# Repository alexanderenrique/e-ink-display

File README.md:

# E-Ink Display

A custom ESP32-C3-based e-ink display platform with a modular app system, BLE configuration, OTA updates, and three KiCad PCB variants. Built around the Seeed XIAO ESP32-C3 and a 2.9" tri-color (black/white/red) e-ink panel (e.g. GDEM029C90).

## Licensing

Hardware design files in [`e-ink-PCBs/`](e-ink-PCBs/) are licensed under **CERN-OHL-W-2.0**. Firmware, scripts, config examples, and Markdown documentation are under the **MIT License**. See [`LICENSE`](LICENSE), [`LICENSE-HARDWARE`](LICENSE-HARDWARE), and [`LICENSE-SOFTWARE`](LICENSE-SOFTWARE).

## Open source scope (third-party parts)

This project is shared to meet the [Open Source Hardware Definition](https://www.oshwa.org/definition/) and aligns with the spirit of [OSHWA certification requirements](https://certification.oshwa.org/requirements.html) for distinguishing parts outside the licensor’s control.

**Released under the licenses above (our work):**

- Schematics and PCB layouts in [`e-ink-PCBs/`](e-ink-PCBs/) (native KiCad sources and Gerber exports in each variant folder).
- Firmware in [`e-ink_code/firmware/`](e-ink_code/firmware/), plus tooling in [`e-ink_code/scripts/`](e-ink_code/scripts/) and examples under [`e-ink_code/config/`](e-ink_code/config/).

**Not open-sourced by this repository (standard commercial / third-party parts; use vendor documentation):**

| Item | Role | Public datasheet / info |
|------|------|-------------------------|
| Seeed XIAO ESP32-C3 | MCU module (ESP32-C3, crystal, antenna, regulators inside module) | Seeed Wiki and [ESP32-C3 technical reference](https://www.espressif.com/en/products/socs/esp32-c3) |
| GDEM029C90 (or compatible Good Display panel) | E-ink panel + timing/controller as supplied by vendor | Vendor PDF (e.g. Good Display product pages) |
| SHT31 | Temperature / humidity sensor IC or module | [Sensirion SHT31 datasheet](https://www.sensirion.com/) |
| FQP27P06, ZXMP4A16G | Discrete MOSFETs | [ON Semi FQP27P06](https://www.onsemi.com/), [Diodes ZXMP4A16G](https://www.diodes.com/) |
| MCP7940N (RTC variant only) | I2C real-time clock | [Microchip MCP7940N](http://ww1.microchip.com/downloads/en/DeviceDoc/20005010F.pdf) |

Optional firmware features (e.g. the **shelf** app) may call HTTP APIs or a companion script (`bin_lookup_server.py`); the hardware and core firmware remain usable without those services.

## Project structure

```
e-ink-display/
├── e-ink-PCBs/                 # KiCad 9 hardware + Gerbers
│   ├── SMD/                    # “SMD” layout variant
│   ├── Throughole-Basic/       # Through-hole, base design
│   ├── Throughole-RTC/         # Through-hole + MCP7940N RTC (+ optional SD header in sch)
│   └── bom/                    # CSV BOM summaries (regenerate from KiCad after edits)
├── e-ink_code/                 # Firmware and scripts (PlatformIO)
│   ├── firmware/               # ESP32-C3 source, core/, apps/, main.cpp
│   ├── scripts/               # OTA, flash, BLE utilities
│   ├── config/examples/       # Device JSON examples
│   ├── platformio.ini
│   └── requirements.txt       # Python deps for helper scripts
├── docs/
│   └── images/                # Add board photos or renders here (recommended for makers)
├── LICENSE, LICENSE-HARDWARE, LICENSE-SOFTWARE, README.md
```

## Hardware

### Components

| Component | Description |
|-----------|-------------|
| Seeed XIAO ESP32-C3 | Microcontroller with WiFi and BLE |
| GDEM029C90 | 2.9" 128×296 tri-color e-ink display (black/white/red) |
| SHT31 | I2C temperature and humidity sensor |
| FQP27P06 (and variants may add ZXMP4A16G) | P-channel MOSFETs for power switching |
| 100 µF capacitor | Bulk decoupling (where present in schematic) |
| Resistors | Voltage divider (47 kΩ / 68 kΩ), pull-ups, etc. (see BOM CSVs) |
| Battery connector | LiPo / battery input |
| Through-hole RTC add-ons (Throughole-RTC only) | MCP7940N, 32.768 kHz crystal, load caps; optional SD header in schematic |

### Pin mapping (ESP32-C3)

| Pin | Function |
|-----|-----------|
| GPIO 3 | SPI SCK (e-ink) |
| GPIO 4 | SPI MOSI (e-ink) |
| GPIO 7 | e-ink CS |
| GPIO 6 | e-ink DC |
| GPIO 5 | e-ink RST |
| GPIO 21 | e-ink BUSY |
| GPIO 9 | I2C SDA (SHT31) |
| GPIO 10 | I2C SCL (SHT31) |
| GPIO 2 | Battery ADC (voltage divider) |
| GPIO 8 | Display + sensor power MOSFET gate |
| GPIO 20 | Battery divider sense enable (`V_SWITCH`) |

### PCB variants

| Directory | Description |
|-----------|-------------|
| [`e-ink-PCBs/SMD/`](e-ink-PCBs/SMD/) | Single main FQP27P06 switch; mixed THT footprints on some passives as in schematic |
| [`e-ink-PCBs/Throughole-Basic/`](e-ink-PCBs/Throughole-Basic/) | Through-hole friendly; includes ZXMP4A16G + FQP27P06 in schematic |
| [`e-ink-PCBs/Throughole-RTC/`](e-ink-PCBs/Throughole-RTC/) | Basic topology + MCP7940N RTC, crystal, optional `J6` SD block |

Each folder contains `.kicad_pro`, `.kicad_sch`, `.kicad_pcb`, drill files, and `*.gbr` / `*.gbrjob` fab outputs. **Preferred source for modification is KiCad**, not Gerbers alone.

### Replication: BOM and assembly

1. Open the variant you are building and use **Tools → Generate Bill of Materials** in KiCad to export a fresh CSV when anything changes.
2. Human-readable summaries for each variant live in [`e-ink-PCBs/bom/`](e-ink-PCBs/bom/) — see [`e-ink-PCBs/bom/README.md`](e-ink-PCBs/bom/README.md).
3. Order PCBs using the `e-ink_PCB-job.gbrjob` or individual Gerbers in that variant’s folder.
4. Solder power, MCU module, and display connector before first power-on; double-check battery polarity and MOSFET orientation against the silkscreen.
5. **First firmware:** flash over USB with PlatformIO (see **Build and flash** below) or keep a personal `e-ink_code/FLASH_INSTRUCTIONS.md` locally (that filename is gitignored).
6. **Photos / renders:** add PNGs under [`docs/images/`](docs/images/) (e.g. bare PCB, populated board, enclosure) so others can verify the build.

## Firmware

### Architecture

The firmware uses a plugin-based app system. Core managers handle hardware (WiFi, display, power, OTA, BLE) and are injected into apps via dependency injection. Each app implements the `AppInterface` and is registered with the `AppManager`, which coordinates lifecycle and configuration.

```
Main  -->  AppManager  -->  [Fun | Sensor | Shelf | Messages]
                |
           Core Managers
       (WiFi, Display, Power, OTA, BLE)
```

### Apps

| App | Description |
|-----|-------------|
| **fun** | Cycles through cat facts, earthquake data, ISS location, useless facts, and local room temperature/humidity. Rotates display mode across deep sleep cycles. |
| **sensor** | Reads temperature and humidity from the SHT31 sensor, displays on screen, and optionally posts data to a Nemo API endpoint. Supports Celsius/Fahrenheit. |
| **shelf** | Queries a bin lookup server to display shelf/bin owner information. Designed for lab inventory labeling. |
| **messages** | Displays a configurable list of up to 10 messages, cycling through them on each wake. |

### BLE configuration

On cold boot (power-on reset), the device advertises via BLE for up to 3 minutes. A BLE central (phone app, script, etc.) can connect and send a JSON configuration including WiFi credentials, app selection, and app-specific settings. The configuration is stored in NVS (non-volatile storage) and persists across deep sleep and reboots.

### Power management

- Battery voltage is read through a 47k/68k resistor divider on GPIO 2.
- Deep sleep is used between display refreshes (configurable per app).
- When battery drops below 5%, the device shows a low-battery message and enters a periodic wake-check sleep (every 5 minutes). Normal operation resumes at 15%.

### OTA updates

The firmware supports HTTPS OTA updates. A deploy script builds the firmware, generates a manifest (version + SHA256), and uploads it to a remote server. Devices check for updates and apply them over WiFi.

### Build environments

Each app has its own PlatformIO build environment that only compiles the code for that specific app:

| Environment | App | Build flag |
|-------------|-----|------------|
| `seeed_xiao_esp32c3` | All apps | (none) |
| `seeed_xiao_fun` | Fun | `-DAPP_FUN` |
| `seeed_xiao_sensor` | Sensor | `-DAPP_SENSOR` |
| `seeed_xiao_shelf` | Shelf | `-DAPP_SHELF` |
| `seeed_xiao_messages` | Messages | `-DAPP_MESSAGES` |

### Dependencies

Managed by PlatformIO (`lib_deps` in `platformio.ini`):

- [GxEPD2](https://github.com/ZinggJM/GxEPD2) — E-ink display driver
- [ArduinoJson](https://github.com/bblanchon/ArduinoJson) ^6.21.3 — JSON parsing
- [Adafruit SHT31 Library](https://github.com/adafruit/Adafruit_SHT31) ^2.2.2 — Temperature/humidity sensor
- [Adafruit Unified Sensor](https://github.com/adafruit/Adafruit_Sensor) ^1.1.9 — Sensor abstraction
- [NimBLE-Arduino](https://github.com/h2zero/NimBLE-Arduino) ^1.4.1 — BLE stack

## Scripts

Located in `e-ink_code/scripts/`:

| Script | Description |
|--------|-------------|
| `deploy_ota.sh` | Build firmware, create manifest, and SCP to OTA server |
| `flash_firmware.sh` | Flash firmware to ESP32-C3 via USB using esptool |
| `bin_lookup_server.py` | Python HTTP server that proxies NEMO API bin/user data for the shelf app |
| `scan_ble.py` | BLE scanner utility to discover and inspect nearby devices |
| `post_build.py` | Copies built firmware binary to `ota/` directory |
| `make_manifest.py` | Generates `manifest.json` with version and SHA256 hash |

## OSHWA certification (administrative next steps)

After this repository reflects the licenses and documentation above, **certification itself is completed on OSHWA’s site**, not in git:

1. Review [Certification requirements](https://certification.oshwa.org/requirements.html) and the [Open Source Hardware checklist](https://www.oshwa.org/resources/open-source-hardware-checklist).
2. Complete the **Certification Mark License Agreement** and submit documentation links for each hardware version you certify.
3. **Register each unique product** that will carry the certification mark, and follow OSHWA’s **mark usage guidelines** (do not imply endorsement by Seeed, Sensirion, Microchip, OSHWA, etc., beyond factual compatibility).
4. Plan for **annual renewal** emails from OSHWA to reaffirm compliance.

Silkscreen and marketing should use only trademarks you are entitled to; third-party logos on the PCB must be cleared separately from this project’s open-license grants.

## Getting started

### Prerequisites

- [PlatformIO](https://platformio.org/) (CLI or IDE plugin)
- [KiCad](https://www.kicad.org/) 9+ (matches current `.kicad_*` schema)
- Python 3 (for utility scripts)

### Build and flash

```bash
cd e-ink_code

# Build a specific app
pio run -e seeed_xiao_sensor

# Upload via USB
pio run -e seeed_xiao_sensor --target upload

# Monitor serial output
pio device monitor
```

### Deploy OTA update

```bash
cd e-ink_code
./scripts/deploy_ota.sh sensor
```

### Run the bin lookup server (shelf app)

```bash
cd e-ink_code
pip install requests python-dotenv
# Set NEMO_API_KEY in a .env file
python scripts/bin_lookup_server.py
```

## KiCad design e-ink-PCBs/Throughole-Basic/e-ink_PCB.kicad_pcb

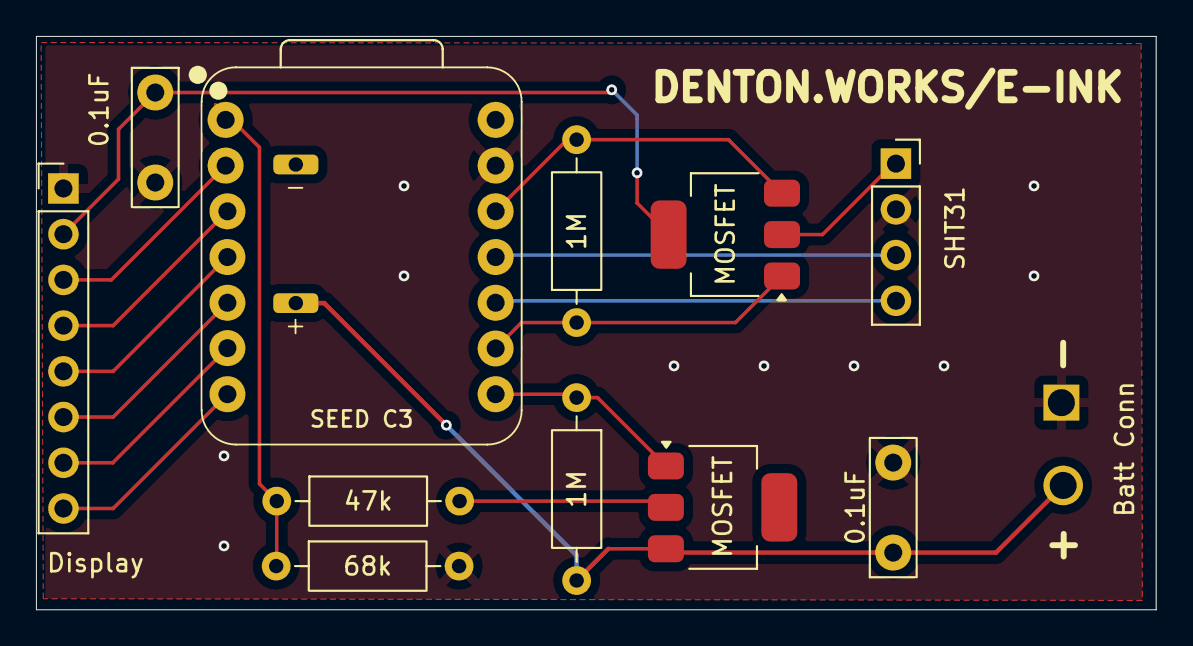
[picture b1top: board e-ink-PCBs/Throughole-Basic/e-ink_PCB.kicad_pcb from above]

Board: 2 copper layers, 62.2 x 31.9 mm, 12 parts (0 on the bottom side), 16 nets.

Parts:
0.1uF, 0.1uF#2: C_Small_US; C_Disc_D7.5mm_W5.0mm_P5.00mm
1M, 47k, 68k: R_Axial_DIN0207_L6.3mm_D2.5mm_P10.16mm_Horizontal
1M#2: 1M; R_Axial_DIN0207_L6.3mm_D2.5mm_P10.16mm_Horizontal
J1: SEED C3; XIAO-ESP32C3-Throughole_alex
J2: e-ink-display; PinHeader_1x08_P2.54mm_Vertical
J3: SHT31; PinSocket_1x04_P2.54mm_Vertical
J5: Batt Conn; PinSocket_1x02_P2.00mm_Vertical
MOSFET: FQP27P06; SOT-223
Q2: MOSFET; SOT-223

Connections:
GND: 0.1uF.2, 0.1uF#2.1, 68k.2, J1.GND (Pin_2), J2.GND (Pin_1), J3.GND (Pin_2), J5.1
unnamed: 47k.1, 68k.1, J1.2 (Pin_8)
unnamed: 0.1uF#2.2, J2.VCC (Pin_2), J3.VIN (Pin_1), Q2.2 (D)
unnamed: J1.3 (Pin_7), J2.SCL (Pin_3)
unnamed: J1.4 (Pin_6), J2.SDA (Pin_4)
unnamed: J1.5, J2.RES (Pin_5)
unnamed: J1.6 (Pin_4), J2.DC (Pin_6)
unnamed: J1.7 (Pin_3), J2.CS (Pin_7)
unnamed: J1.21 (Pin_2), J2.BUSY (Pin_8)
unnamed: J1.10 (Pin_4), J3.SCL (Pin_3)
unnamed: J1.9 (Pin_5), J3.SDA (Pin_4)
unnamed: 0.1uF.1, 1M#2.2, J1.BAT+ (Pin_1), J5.2, MOSFET.3 (S)
unnamed: 47k.2, MOSFET.2 (D)
unnamed: 1M#2.1, J1.20 (Pin_7), MOSFET.1 (G)
unnamed: 1M.1, J1.8 (Pin_6), Q2.1 (G)
unnamed: 1M.2, J1.3.3V (Pin_3), Q2.3 (S)

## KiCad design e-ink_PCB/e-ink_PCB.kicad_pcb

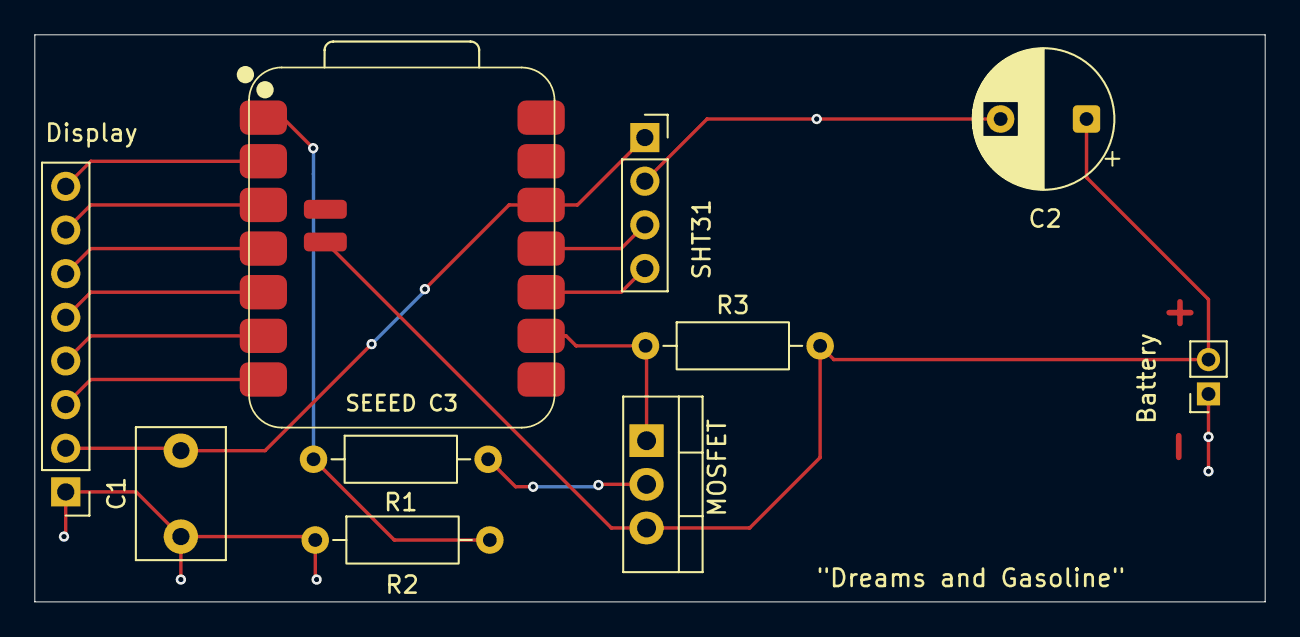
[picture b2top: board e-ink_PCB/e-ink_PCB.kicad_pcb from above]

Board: 2 copper layers, 71.6 x 33.0 mm, 10 parts (0 on the bottom side), 14 nets.

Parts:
C1: C_Small_US; C_Disc_D7.5mm_W5.0mm_P5.00mm
Display: e-ink-display; PinHeader_1x08_P2.54mm_Vertical
J1: SEEED C3; XIAO-ESP32C3-SMD_alex
J3: SHT31; PinSocket_1x04_P2.54mm_Vertical
J4: C2; CP_Radial_D8.0mm_P5.00mm
J5: Battery; PinSocket_1x02_P2.00mm_Vertical
MOSFET: FQP27P06; TO-220-3_Vertical
R1, R2, R3: R_Small_US; R_Axial_DIN0207_L6.3mm_D2.5mm_P10.16mm_Horizontal

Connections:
GND: C1.1, Display.GND (Pin_1), J1.BAT- (Pin_1), J1.GND (Pin_2), J3.GND (Pin_2), J4.- (Pin_1), J5.1, R2.1
unnamed: J1.2 (Pin_8), R1.1, R2.2
unnamed: C1.2, Display.VCC (Pin_2), J1.3.3V (Pin_3), J3.VIN (Pin_1)
unnamed: Display.SCL (Pin_3), J1.21 (Pin_2)
unnamed: Display.SDA (Pin_4), J1.7 (Pin_3)
unnamed: Display.RES (Pin_5), J1.6 (Pin_4)
unnamed: Display.DC (Pin_6), J1.5
unnamed: Display.CS (Pin_7), J1.4 (Pin_6)
unnamed: Display.BUSY (Pin_8), J1.3 (Pin_7)
unnamed: J1.10 (Pin_4), J3.SCL (Pin_3)
unnamed: J1.9 (Pin_5), J3.SDA (Pin_4)
unnamed: J1.BAT+ (Pin_1), J4.+ (Pin_2), J5.2, MOSFET.3 (S), R3.2
unnamed: MOSFET.2 (D), R1.2
unnamed: J1.8 (Pin_6), MOSFET.1 (G), R3.1

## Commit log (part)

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2026-01-22 Initial commit: e-ink display project
2026-01-23 added APIs, wifi strength check, deep sleep
2026-01-24 working battery voltage
2026-01-24 fine tuning battery voltage
2026-01-25 adding KiCAD
2026-01-25 kiCAD correct display orientation
2026-01-26 kiCAD shipped
2026-01-26 seperated files by functionality, added flash partitioning
2026-01-28 throughole design
2026-01-28 Remove secure_boot_signing_key.pem from tracking and add to .gitignore
2026-01-29 migration complete?
2026-02-01 working OTA
2026-02-02 restructured firmware
2026-02-03 seperated compiling
2026-02-03 moved to nimBLE, BLE troubleshooting
2026-02-03 ble work
2026-02-03 Ignore e-ink_code/venv
2026-02-03 requirements
2026-02-03 working BLE, receiving it too
2026-02-04 BLE working, including reboot
2026-02-04 working, added BLE config screen
2026-02-04 Pretty close on the sensor
2026-02-05 accepts multiple sensor fields
2026-02-05 Checkpoint, web upload working
2026-02-06 added battery low message
2026-02-06 done for todday
2026-02-09 going to work
2026-02-10 added messages
2026-02-10 formatting improvements
2026-02-11 added ota upload bash
2026-02-11 updates to KiCAD
2026-02-11 added readme
2026-03-02 sensor firmware now pushes to nemo
2026-03-09 folder re-org, MOSFET design
2026-03-09 almost final throughole-basic
2026-03-17 added time, new PCB design
2026-03-24 changes to sensor code
2026-05-09 almost OSHWA ready
2026-05-12 updated the ISS code
2026-05-13 fun mode server added
2026-05-14 updated formatting, gitignore hardware_config
2026-05-16 getting the server working
2026-05-16 anydiff
2026-05-19 ISS bug
2026-05-19 added oceans
